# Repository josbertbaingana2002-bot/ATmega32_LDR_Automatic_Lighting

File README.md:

# ATmega32_LDR_Automatic_Lighting
Automatic Lighting System using ATmega32, LDR, KiCad and SimulIDE

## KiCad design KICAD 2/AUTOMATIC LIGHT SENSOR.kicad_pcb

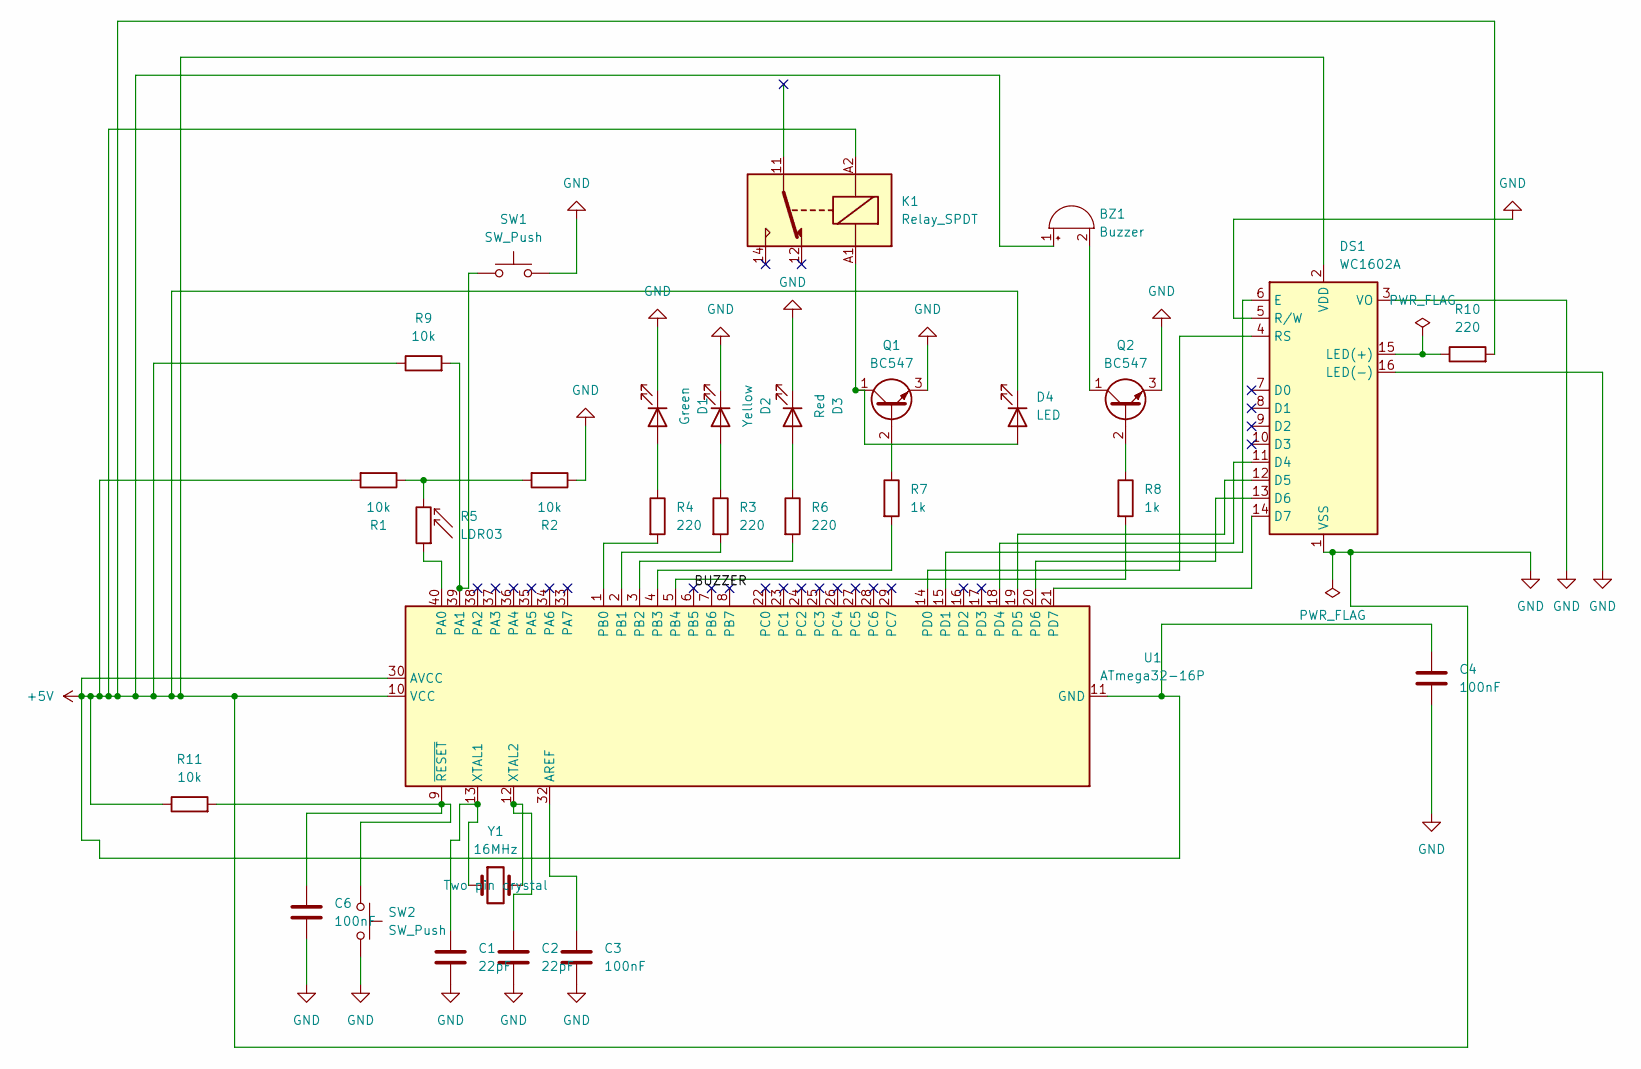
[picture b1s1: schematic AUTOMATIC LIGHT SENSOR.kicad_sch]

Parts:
BZ1: Buzzer; Buzzer_12x9.5RM7.6
C1, C2: 22pF; C_Disc_D5.0mm_W2.5mm_P5.00mm
C3, C4, C6: 100nF; C_Disc_D5.0mm_W2.5mm_P5.00mm
D1: Green; LED_D5.0mm
D2: Yellow; LED_D5.0mm
D3: Red; LED_D5.0mm
D4: LED; LED_D5.0mm
DS1: WC1602A
K1: Relay_SPDT; Relay_SPDT_CUI_SR5
Q1, Q2: BC547; TO-92_Inline
R1, R2, R9, R11: 10k; R_Axial_DIN0207_L6.3mm_D2.5mm_P7.62mm_Horizontal
R3, R4, R6, R10: 220; R_Axial_DIN0207_L6.3mm_D2.5mm_P7.62mm_Horizontal
R5: LDR03; R_LDR_10x8.5mm_P7.6mm_Vertical
R7, R8: 1k; R_Axial_DIN0207_L6.3mm_D2.5mm_P7.62mm_Horizontal
SW1, SW2: SW_Push; SW_PUSH_6mm
U1: ATmega32-16P; DIP-40_W15.24mm
Y1: 16MHz; Crystal_HC49-U_Vertical

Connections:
/BUZZER: U1.6 (PB5)
unnamed: BZ1.2 (-), Q2.1 (C)
unnamed: D1.2 (A), R4.1
unnamed: D2.2 (A), R3.1
unnamed: D3.2 (A), R6.1
unnamed: D4.2 (A), K1.A1, Q1.1 (C)
unnamed: DS1.11 (D4), U1.18 (PD4)
unnamed: DS1.12 (D5), U1.19 (PD5)
unnamed: DS1.13 (D6), U1.20 (PD6)
unnamed: DS1.14 (D7), U1.21 (PD7)
unnamed: DS1.6 (E), U1.15 (PD1)
unnamed: DS1.15 (LED(+)), R10.1
unnamed: DS1.4 (RS), U1.14 (PD0)
unnamed: Q1.2 (B), R7.1
unnamed: Q2.2 (B), R8.1
unnamed: R1.1, R2.2, R5.2
unnamed: C3.1, U1.32 (AREF)
unnamed: R5.1, U1.40 (PA0)
unnamed: R9.2, SW1.1, U1.39 (PA1)
unnamed: R4.2, U1.1 (PB0)
unnamed: R3.2, U1.2 (PB1)
unnamed: R6.2, U1.3 (PB2)
unnamed: R7.2, U1.4 (PB3)
unnamed: R8.2, U1.5 (PB4)
unnamed: C1.1, U1.13 (XTAL1), Y1.1
unnamed: C2.1, U1.12 (XTAL2), Y1.2
unnamed: C6.1, R11.2, SW2.1, U1.9 (~RESET)

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
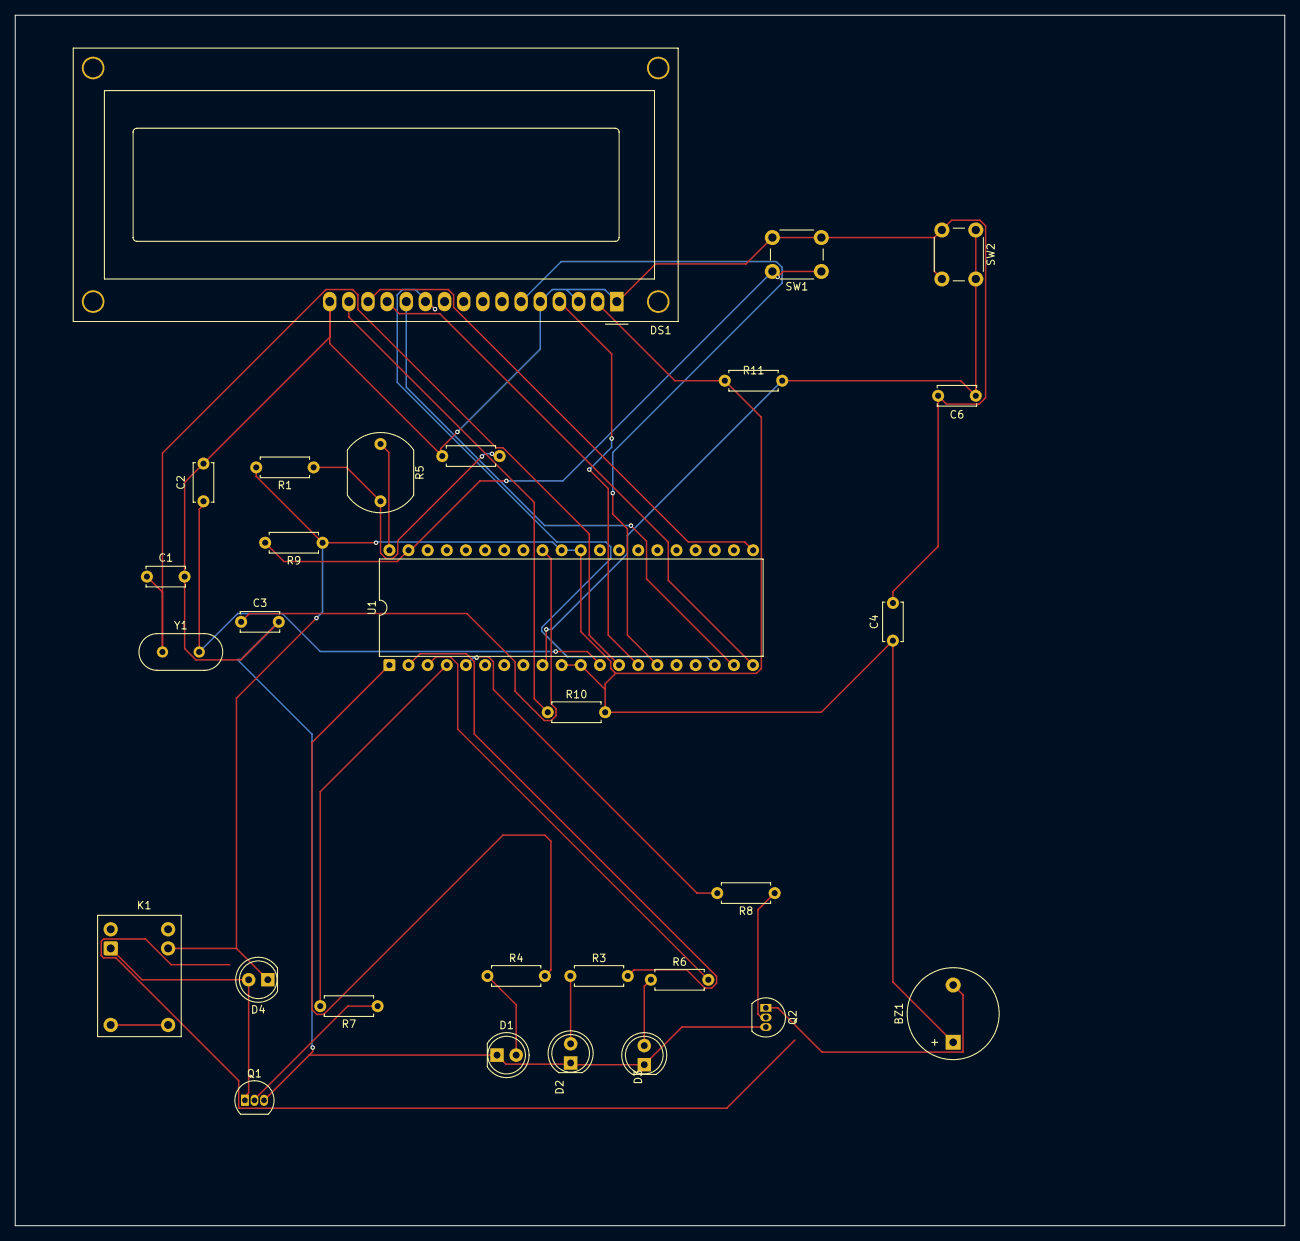
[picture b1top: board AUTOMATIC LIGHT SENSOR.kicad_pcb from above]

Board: 2 copper layers, 168.5 x 160.6 mm, 29 parts (0 on the bottom side), 28 nets.

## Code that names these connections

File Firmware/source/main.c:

#define F_CPU 16000000UL
#include "lcd.h"
#include <avr/io.h>
#include <stdlib.h> 
#include <util/delay.h>

// --- ADC Initialization ---
void ADC_Init() {
    ADMUX  = (1 << REFS0);
    ADCSRA = (1 << ADEN) | (1 << ADPS2) | (1 << ADPS1);
}

uint16_t ReadADC(uint8_t channel) {
    ADMUX &= 0xF0;
    ADMUX |= channel;
    ADCSRA |= (1 << ADSC);
    while (ADCSRA & (1 << ADSC));
    return ADC;
}

// --- Thresholds ---
#define BRIGHT_THRESHOLD   800
#define MEDIUM_THRESHOLD   600
#define LOW_THRESHOLD      400

// --- Pin Definitions ---
uint8_t manualMode = 0;
uint8_t lampState  = 0;
uint8_t btnPrev    = 1;
uint16_t prevLight = 9999; 
uint8_t prevMode   = 255;  

// --- LCD Number Print ---
void LCD_PrintNum(uint16_t num) {
    char buf[6];
    uint8_t i = 0;
    if (num == 0) { LCD_Char('0'); return; }
    while (num > 0) {
        buf[i++] = '0' + (num % 10);
        num /= 10;
    }
    for (int j = i - 1; j >= 0; j--) {
        LCD_Char(buf[j]);
    }
}

// --- Clear All Outputs ---
void Clear_Outputs() {
    PORTB &= ~((1 << PB0) | (1 << PB1) | (1 << PB2) | (1 << PB3) | (1 << PB4));
}

int main(void) {
    // GPIO Initialization
    DDRA  = 0x00;
    PORTA = (1 << PA1);         // Pull-up on override button
    DDRB  = 0x1F;               // PB0-PB4 outputs
    PORTB = 0x00;
    DDRC  = 0x00;
    PORTC = 0x00;
    DDRD  = 0xFF;               // LCD Data/Control lines
    PORTD = 0x00;

    ADC_Init();
    LCD_Init();

    // System Startup Screen
    LCD_SetCursor(1, 1);
    LCD_String("SMART LIGHT");
    LCD_SetCursor(2, 1);
    LCD_String("SYSTEM READY");
    _delay_ms(2000);
    LCD_Clear();

    while (1) {
        // --- Button Edge Detection ---
        uint8_t btnNow = (PINA & (1 << PA1)) ? 1 : 0;
        if (btnPrev == 1 && btnNow == 0) { 
            _delay_ms(20);                 
            if (!(PINA & (1 << PA1))) {    
                if (!manualMode) {
                    manualMode = 1;
                    lampState = 1;         
                } else {
                    manualMode = 0;        // Pressing it again exits manual mode back to auto
                }
                prevLight = 9999;          
                _delay_ms(200); 
            }
        }
        btnPrev = btnNow;

        // --- ADC Reading ---
        uint16_t light = ReadADC(0);

        // --- Mode Logic and Pin Control ---
        if (manualMode) {
            PORTB &= ~((1 << PB0) | (1 << PB1) | (1 << PB2) | (1 << PB4)); 
            if (lampState) PORTB |= (1 << PB3);
            else           PORTB &= ~(1 << PB3);
        } 
        else {
            // Automatic Hardware Control
            if (light > BRIGHT_THRESHOLD) {
                PORTB &= ~((1 << PB0) | (1 << PB1) | (1 << PB3) | (1 << PB4));
                PORTB |=  (1 << PB2); // Green LED ON
            } else if (light > MEDIUM_THRESHOLD) {
                PORTB &= ~((1 << PB0) | (1 << PB2) | (1 << PB3) | (1 << PB4));
                PORTB |=  (1 << PB1); // Yellow LED ON
            } else if (light > LOW_THRESHOLD) {
                PORTB &= ~((1 << PB1) | (1 << PB2) | (1 << PB4));
                PORTB |=  (1 << PB0) | (1 << PB3); // Red LED and Lamp ON
            } else {
                // VERY LOW LIGHT: Triggers cleanly for anything below 401
                PORTB &= ~((1 << PB1) | (1 << PB2));
                PORTB |=  (1 << PB0) | (1 << PB3); // Red LED and Lamp ON
                
                PORTB |= (1 << PB4);  // Turn Buzzer ON
                _delay_ms(100);
                PORTB &= ~(1 << PB4); // Turn Buzzer OFF
            }
        }

        // --- Display Control ---
        int16_t diff = (int16_t)light - (int16_t)prevLight;
        if (abs(diff) > 5 || manualMode != prevMode) {
            LCD_Clear();
            
            if (manualMode) {
                LCD_SetCursor(1, 1);
                LCD_String("MANUAL MODE");
                LCD_SetCursor(2, 1);
                LCD_String(lampState ? "LAMP: ON " : "LAMP: OFF");
            } 
            else {
                LCD_SetCursor(1, 1);
                LCD_String("ADC: ");
                LCD_PrintNum(light);
                
                LCD_SetCursor(2, 1);
                if (light > BRIGHT_THRESHOLD)        LCD_String("BRIGHT LAMP:OFF");
                else if (light > MEDIUM_THRESHOLD)   LCD_String("MEDIUM LAMP:OFF");
                else if (light > LOW_THRESHOLD)      LCD_String("LOW    LAMP:ON ");
                else                                 LCD_String("V.LOW  LAMP:ON ");
            }
            
            prevLight = light;
            prevMode = manualMode;
        }

        _delay_ms(50); 
    }
    return 0;
}
